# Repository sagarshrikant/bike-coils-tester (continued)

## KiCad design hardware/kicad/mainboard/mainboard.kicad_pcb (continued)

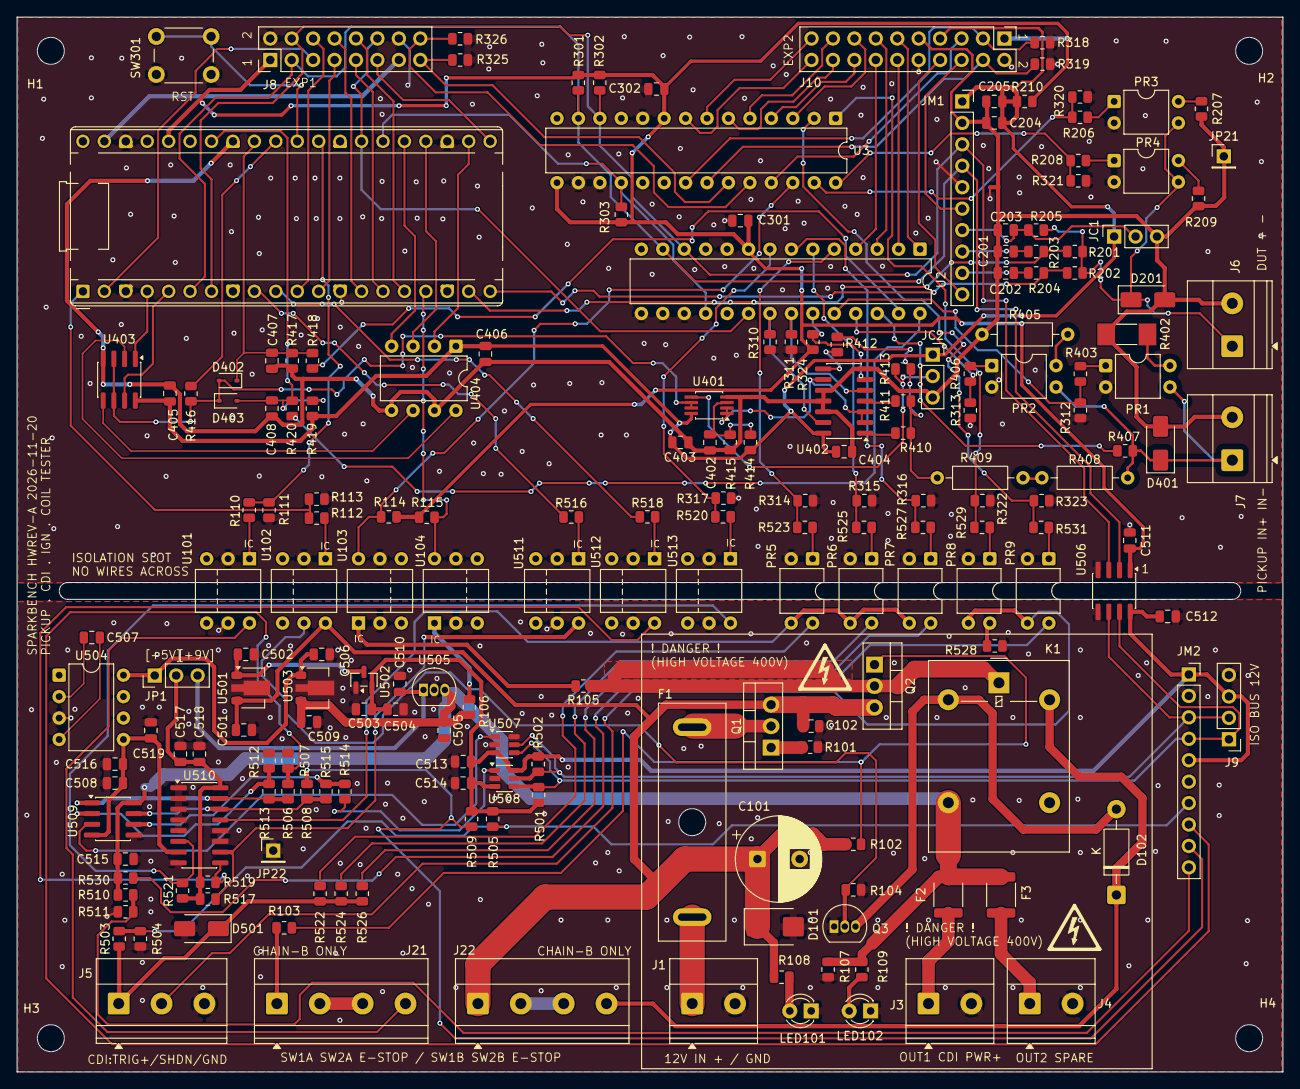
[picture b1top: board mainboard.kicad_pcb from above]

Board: 2 copper layers, 150.0 x 125.0 mm, 202 parts (0 on the bottom side), 152 nets.

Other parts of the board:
H1, H2, H3, H4: MountingHole_3.2mm_M3
